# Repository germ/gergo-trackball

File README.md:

# gBallin Trackball

KiCad files for the gBallin

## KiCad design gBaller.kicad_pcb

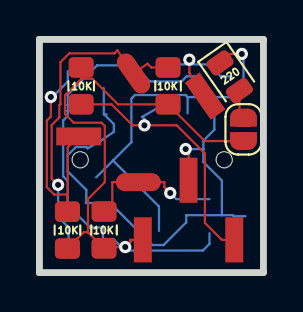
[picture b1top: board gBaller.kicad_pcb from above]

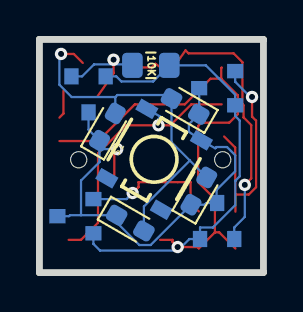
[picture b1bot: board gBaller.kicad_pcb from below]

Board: 2 copper layers, 12.4 x 13.0 mm, 20 parts (11 on the bottom side), 9 nets.

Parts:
D23, D52, D53, D54: LED; D_0603_1608Metric_Pad1.05x0.95mm_HandSolder
J5: M4; PinHeader_1x02_P2.54mm_Vertical_SMD_Pin1Right
J7: M5; PinHeader_1x03_P2.54mm_Vertical_SMD_Pin1Left
J9: M6; PinHeader_1x02_P2.54mm_Vertical_SMD_Pin1Left
JP1: JUMPER; SolderJumper-2_P1.3mm_Open_RoundedPad1.0x1.5mm
R3, R4, R5, R6, R7: 10K; R_0805_2012Metric_Pad1.15x1.40mm_HandSolder
R12: 220; D_0805_2012Metric
S1: TB_Button; TACTILE_SWITCH_SMD-2
TB1: TRACKBALLMECH; TRACKBALL
U3, U4, U5, U6: SM351LT; SOT-23

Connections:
/M1: J5.2, R3.2, U3.2
/M2: J5.1, R4.2, U4.2
/M3: J9.2, R6.2, U5.2
/M4: J9.1, R7.2, U6.2
/M5: J7.3, R5.2, S1.1
GND: D23.1, D52.1, D53.1, D54.1, J7.2, S1.2, U3.3, U4.3, U5.3, U6.3
unnamed: D23.2, D52.2, D53.2, D54.2, R12.1
unnamed: JP1.2, R12.2
VCC: J7.1, JP1.1, R3.1, R4.1, R5.1, R6.1, R7.1, U3.1, U4.1, U5.1, U6.1
